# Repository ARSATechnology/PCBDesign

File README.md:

# PCBDesign

In this Github Site we share some of our PCB Design for Automation & IoT projects.
You can use the design to learn electronics, or to make a commercial product

Thank you

Best,

Hilmy Izzulhaq

Founder & CEO ARSA Technology

hilmy@arsa.tech

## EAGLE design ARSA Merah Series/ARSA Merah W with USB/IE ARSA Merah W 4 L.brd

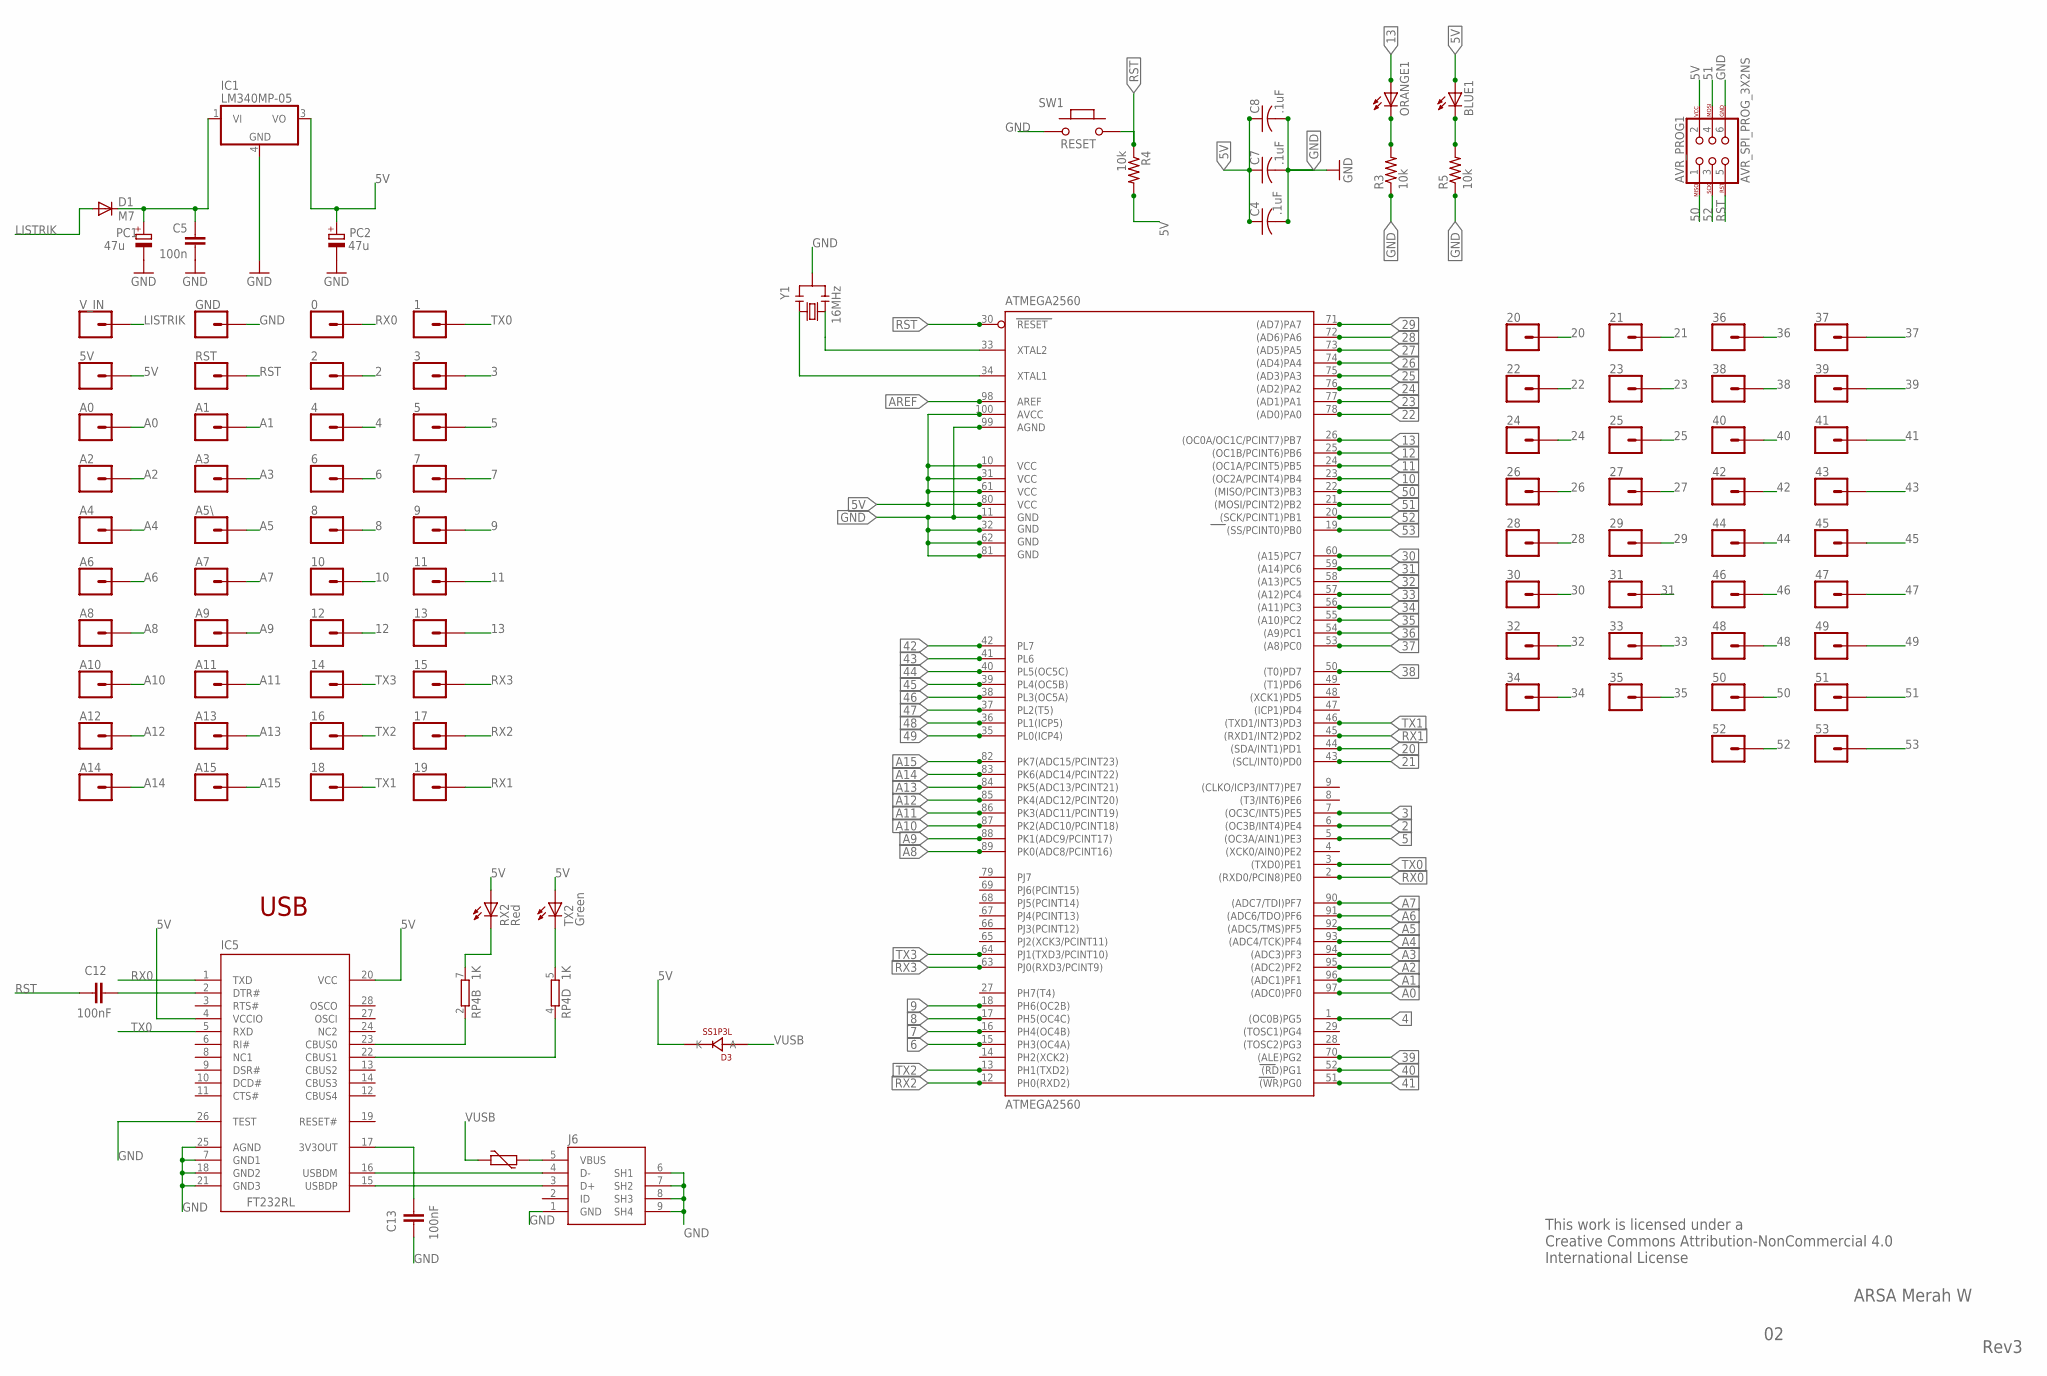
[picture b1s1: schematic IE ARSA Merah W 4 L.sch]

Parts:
0, 1, 2, 3, 4, 5, 5V, 6, 7, 8, 9, 10, 11, 12, 13, 14, 15, 16, 17, 18, 19, 20, 21, 22, 23, 24, 25, 26, 27, 28, 29, 30, 31, 32, 33, 34, 35, 36, 37, 38, 39, 40, 41, 42, 43, 44, 45, 46, 47, 48, 49, 50, 51, 52, 53: CONN_01; 1X01
A0, A1, A2, A3, A4, A5\, A6, A7, A8, A9, A10, A11, A12, A13, A14, A15: CONN_01; 1X01
ATMEGA2560: ATMEGA2560; TQFP100
AVR_PROG1: AVR_SPI_PROG_3X2NS; 2X3-NS
BLUE1: L; SMD-0805-LED
C4: CAPACITOR-SMD-0805; SMD-0805
C5: 100n; C0603-ROUND
C7, C8: .1uF; SMD-0805
C12, C13: 100nF; C0603-ROUND
D1: M7; SMB
D3: SS1P3L; DO220AAL
F3: MFFSMF050; 0603-1608X90N
GND: CONN_01; 1X01
IC1: LM340MP-05; SOT223
IC5: FT232RL; SSOP28
J6: 0219_14850; USB-MINI-B_2
ORANGE1: L; SMD-0805-LED
PC1, PC2: 47u; PANASONIC_D
R3, R4, R5: 10k; SMD-0805
RP4: 1K; CAY16
RST: CONN_01; 1X01
RX2: Red; CHIPLED_0805
SW1: RESET; SMD_157SW
TX2: Green; CHIPLED_0805
V_IN: CONN_01; 1X01
Y1: 16MHz; RESONATOR

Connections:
2: 2.1, ATMEGA2560.6 ((OC3B/INT4)PE4)
3: 3.1, ATMEGA2560.7 ((OC3C/INT5)PE5)
4: 4.1, ATMEGA2560.1 ((OC0B)PG5)
5: 5.1, ATMEGA2560.5 ((OC3A/AIN1)PE3)
5V: 5V.1, ATMEGA2560.10 (VCC), ATMEGA2560.31 (VCC1), ATMEGA2560.61 (VCC2), ATMEGA2560.80 (VCC3), ATMEGA2560.100 (AVCC), AVR_PROG1.2, BLUE1.1 (A), C4.1, C7.1, C8.1, D3.P$1 (K), IC1.3 (VO), IC5.4 (VCCIO), IC5.20 (VCC), PC2.+, R4.2, RX2.A, TX2.A
6: 6.1, ATMEGA2560.15 (PH3(OC4A))
7: 7.1, ATMEGA2560.16 (PH4(OC4B))
8: 8.1, ATMEGA2560.17 (PH5(OC4C))
9: 9.1, ATMEGA2560.18 (PH6(OC2B))
10: 10.1, ATMEGA2560.23 ((OC2A/PCINT4)PB4)
11: 11.1, ATMEGA2560.24 ((OC1A/PCINT5)PB5)
12: 12.1, ATMEGA2560.25 ((OC1B/PCINT6)PB6)
13: 13.1, ATMEGA2560.26 ((OC0A/OC1C/PCINT7)PB7), ORANGE1.1 (A)
20: 20.1, ATMEGA2560.44 ((SDA/INT1)PD1)
21: 21.1, ATMEGA2560.43 ((SCL/INT0)PD0)
22: 22.1, ATMEGA2560.78 ((AD0)PA0)
23: 23.1, ATMEGA2560.77 ((AD1)PA1)
24: 24.1, ATMEGA2560.76 ((AD2)PA2)
25: 25.1, ATMEGA2560.75 ((AD3)PA3)
26: 26.1, ATMEGA2560.74 ((AD4)PA4)
27: 27.1, ATMEGA2560.73 ((AD5)PA5)
28: 28.1, ATMEGA2560.72 ((AD6)PA6)
29: 29.1, ATMEGA2560.71 ((AD7)PA7)
30: 30.1, ATMEGA2560.60 ((A15)PC7)
31: 31.1, ATMEGA2560.59 ((A14)PC6)
32: 32.1, ATMEGA2560.58 ((A13)PC5)
33: 33.1, ATMEGA2560.57 ((A12)PC4)
34: 34.1, ATMEGA2560.56 ((A11)PC3)
35: 35.1, ATMEGA2560.55 ((A10)PC2)
36: 36.1, ATMEGA2560.54 ((A9)PC1)
37: 37.1, ATMEGA2560.53 ((A8)PC0)
38: 38.1, ATMEGA2560.50 ((T0)PD7)
39: 39.1, ATMEGA2560.70 ((ALE)PG2)
40: 40.1, ATMEGA2560.52 ((RD)PG1)
41: 41.1, ATMEGA2560.51 ((WR)PG0)
42: 42.1, ATMEGA2560.42 (PL7)
43: 43.1, ATMEGA2560.41 (PL6)
44: 44.1, ATMEGA2560.40 (PL5(OC5C))
45: 45.1, ATMEGA2560.39 (PL4(OC5B))
46: 46.1, ATMEGA2560.38 (PL3(OC5A))
47: 47.1, ATMEGA2560.37 (PL2(T5))
48: 48.1, ATMEGA2560.36 (PL1(ICP5))
49: 49.1, ATMEGA2560.35 (PL0(ICP4))
50: 50.1, ATMEGA2560.22 ((MISO/PCINT3)PB3), AVR_PROG1.1
51: 51.1, ATMEGA2560.21 ((MOSI/PCINT2)PB2), AVR_PROG1.4
52: 52.1, ATMEGA2560.20 ((SCK/PCINT1)PB1), AVR_PROG1.3
53: 53.1, ATMEGA2560.19 ((SS/PCINT0)PB0)
A0: A0.1, ATMEGA2560.97 ((ADC0)PF0)
A1: A1.1, ATMEGA2560.96 ((ADC1)PF1)
A2: A2.1, ATMEGA2560.95 ((ADC2)PF2)
A3: A3.1, ATMEGA2560.94 ((ADC3)PF3)
A4: A4.1, ATMEGA2560.93 ((ADC4/TCK)PF4)
A5: A5\.1, ATMEGA2560.92 ((ADC5/TMS)PF5)
A6: A6.1, ATMEGA2560.91 ((ADC6/TDO)PF6)
A7: A7.1, ATMEGA2560.90 ((ADC7/TDI)PF7)
A8: A8.1, ATMEGA2560.89 (PK0(ADC8/PCINT16))
A9: A9.1, ATMEGA2560.88 (PK1(ADC9/PCINT17))
A10: A10.1, ATMEGA2560.87 (PK2(ADC10/PCINT18))
A11: A11.1, ATMEGA2560.86 (PK3(ADC11/PCINT19))
A12: A12.1, ATMEGA2560.85 (PK4(ADC12/PCINT20))
A13: A13.1, ATMEGA2560.84 (PK5(ADC13/PCINT21))
A14: A14.1, ATMEGA2560.83 (PK6(ADC14/PCINT22))
A15: A15.1, ATMEGA2560.82 (PK7(ADC15/PCINT23))
AREF: ATMEGA2560.98 (AREF)
GND: ATMEGA2560.11 (GND), ATMEGA2560.32 (GND1), ATMEGA2560.62 (GND2), ATMEGA2560.81 (GND3), ATMEGA2560.99 (AGND), AVR_PROG1.6, C4.2, C5.2, C7.2, C8.2, C13.1, GND.1, IC1.4 (GND), IC5.7 (GND1), IC5.18 (GND2), IC5.21 (GND3), IC5.25 (AGND), IC5.26 (TEST), J6.1 (GND), J6.6 (SH1), J6.7 (SH2), J6.8 (SH3), J6.9 (SH4), PC1.-, PC2.-, R3.1, R5.1, SW1.1, Y1.2
LISTRIK: D1.A, V_IN.1
unnamed: ORANGE1.2 (C), R3.2
unnamed: ATMEGA2560.33 (XTAL2), Y1.3
unnamed: BLUE1.2 (C), R5.2
unnamed: ATMEGA2560.34 (XTAL1), Y1.1
unnamed: C12.2, IC5.2 (DTR#)
unnamed: IC5.15 (USBDP), J6.3 (D+)
unnamed: IC5.16 (USBDM), J6.4 (D-)
unnamed: IC5.23 (CBUS0), RP4.2 (1)
unnamed: IC5.22 (CBUS1), RP4.4 (1)
unnamed: RP4.5 (2), TX2.C
unnamed: F3.2, J6.5 (VBUS)
unnamed: RP4.7 (2), RX2.C
unnamed: C13.2, IC5.17 (3V3OUT)
RST: ATMEGA2560.30 (RESET), AVR_PROG1.5, C12.1, R4.1, RST.1, SW1.2
RX0: 0.1, ATMEGA2560.2 ((RXD0/PCIN8)PE0), IC5.1 (TXD)
RX1: 19.1, ATMEGA2560.45 ((RXD1/INT2)PD2)
RX2: 17.1, ATMEGA2560.12 (PH0(RXD2))
RX3: 15.1, ATMEGA2560.63 (PJ0(RXD3/PCINT9))
TX0: 1.1, ATMEGA2560.3 ((TXD0)PE1), IC5.5 (RXD)
TX1: 18.1, ATMEGA2560.46 ((TXD1/INT3)PD3)
TX2: 16.1, ATMEGA2560.13 (PH1(TXD2))
TX3: 14.1, ATMEGA2560.64 (PJ1(TXD3/PCINT10))
VIN: C5.1, D1.C, IC1.1 (VI), PC1.+
VUSB: D3.P$2 (A), F3.1

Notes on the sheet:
.1uF
ARSA Merah W
Rev3
This work is licensed under a Creative Commons Attribution-NonCommercial 4.0 International License
USB

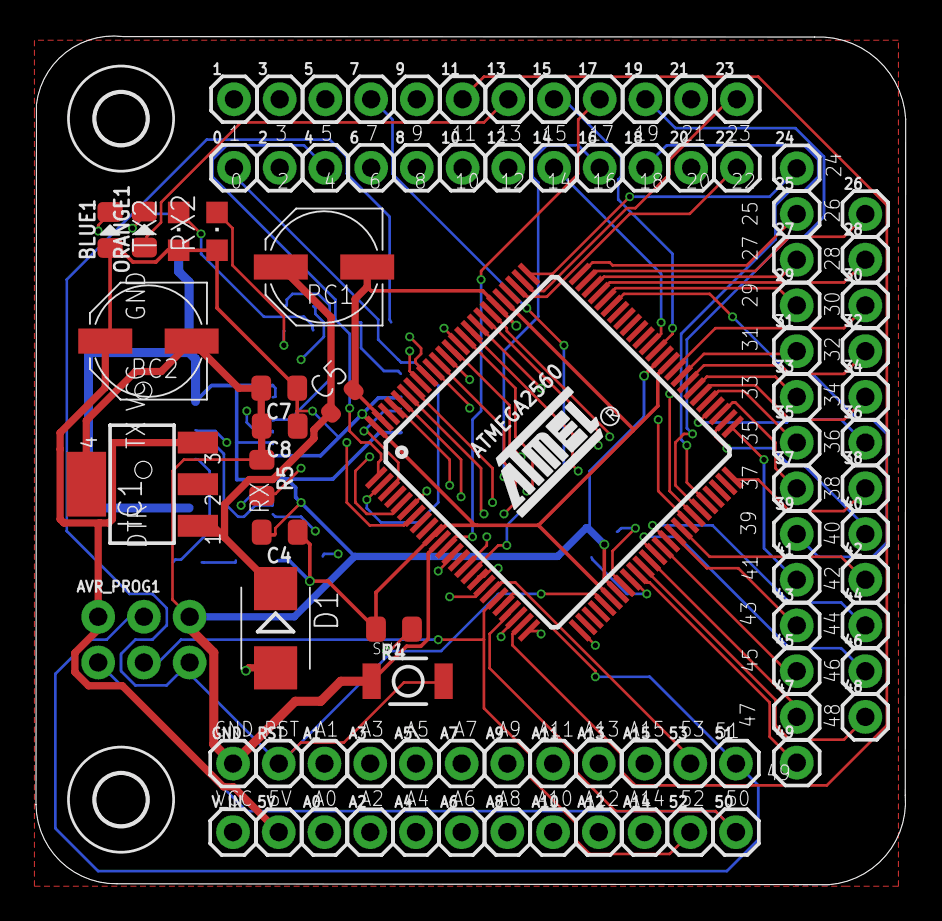
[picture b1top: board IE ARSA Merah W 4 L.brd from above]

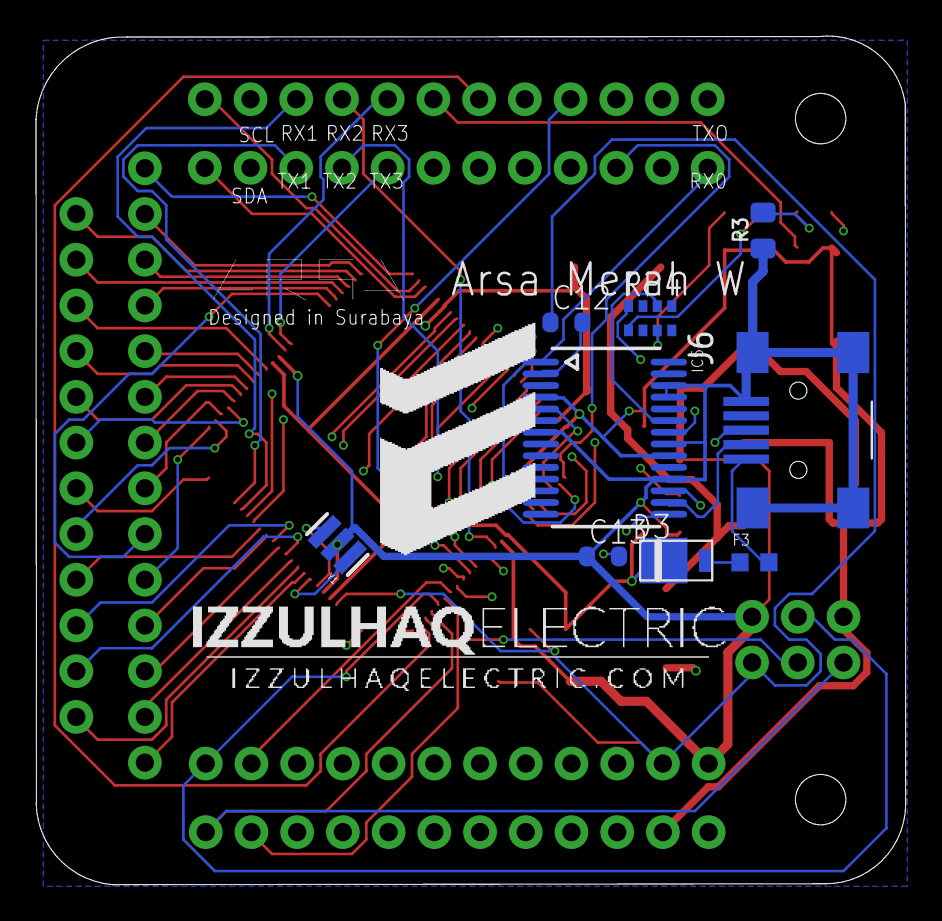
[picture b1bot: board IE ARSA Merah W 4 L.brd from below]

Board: 4 copper layers, 48.3 x 47.1 mm, 102 parts (9 on the bottom side), 89 nets.

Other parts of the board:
U$1, U$2: 2,8

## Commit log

2019-06-22 Create ARSA Merah W
2019-06-22 Create ARSA Merah W with USB
2019-06-22 Create ARSA Merah Mini

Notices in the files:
parts and their libraries:
SparkFun-Connectors: Licensing: Creative Commons ShareAlike 4.0 International - https://creativecommons.org/licenses/by-sa/4.0
Arduino-rcl: Copyright (c) 2016-2017 Arduino LLC.  All right reserved.
